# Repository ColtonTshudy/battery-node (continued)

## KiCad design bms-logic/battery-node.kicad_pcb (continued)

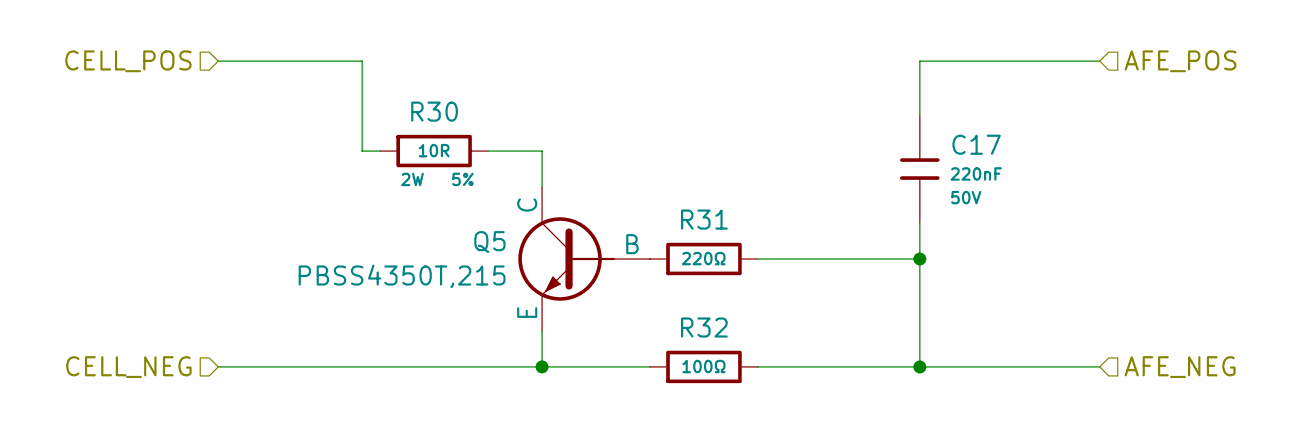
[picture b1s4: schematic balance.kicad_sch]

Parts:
C17: 220nF; C_0805; Voltage Rated 50V; Tolerance ±10%; Part CL21B224KBFNNNE; LCSC C5378
Q5: PBSS4350T,215; SOT-23; Part PBSS4350T,215
R30: 10R; R_2512_6332Metric; Tolerance 5%; Part FRP2512J100 TS
R31: 220Ω; R_0402; Tolerance ±1%; Overload Voltage (Max) 50V; Part 0402WGF2200TCE; LCSC C25091
R32: 100Ω; R_0402; Overload Voltage (Max) 50V; Tolerance ±1%; Part 0402WGF1000TCE; LCSC C25076

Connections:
/AFE/Cell1: Q5.2 (E), R32.1; also elsewhere on the board
/AFE/Cell2: R30.2; also elsewhere on the board
/AFE/VC1: C17.2, R31.2, R32.2; also elsewhere on the board
/AFE/VC2: C17.1; also elsewhere on the board
unnamed: Q5.1 (B), R31.1
unnamed: Q5.3 (C), R30.1

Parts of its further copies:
C36, C37, C38, C39, C40, C41, C42, C43, C44, C45, C46, C47, C48, C49: 220nF; C_0805; Voltage Rated 50V; Tolerance ±10%; Part CL21B224KBFNNNE; LCSC C5378
Q6, Q7, Q8, Q9, Q10, Q11, Q12, Q13, Q14, Q15, Q16, Q17, Q18, Q19: PBSS4350T,215; SOT-23; Part PBSS4350T,215
R48, R51, R54, R57, R60, R63, R66, R69, R72, R75, R78, R81, R84, R87: 10R; R_2512_6332Metric; Tolerance 5%; Part FRP2512J100 TS
R49, R52, R55, R58, R61, R64, R67, R70, R73, R76, R79, R82, R85, R88: 220Ω; R_0402; Tolerance ±1%; Overload Voltage (Max) 50V; Part 0402WGF2200TCE; LCSC C25091
R50, R53, R56, R59, R62, R65, R68, R71, R74, R77, R80, R83, R86, R89: 100Ω; R_0402; Overload Voltage (Max) 50V; Tolerance ±1%; Part 0402WGF1000TCE; LCSC C25076

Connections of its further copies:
/AFE/Cell2: Q6.2 (E), R50.1; also elsewhere on the board
/AFE/Cell3: Q7.2 (E), R48.2, R53.1; also elsewhere on the board
/AFE/Cell4: Q8.2 (E), R51.2, R56.1; also elsewhere on the board
/AFE/Cell5: Q9.2 (E), R54.2, R59.1; also elsewhere on the board
/AFE/Cell6: Q10.2 (E), R57.2, R62.1; also elsewhere on the board
/AFE/Cell7: Q11.2 (E), R60.2, R65.1; also elsewhere on the board
/AFE/Cell8: Q12.2 (E), R63.2, R68.1; also elsewhere on the board
/AFE/Cell9: Q13.2 (E), R66.2, R71.1; also elsewhere on the board
/AFE/Cell10: Q14.2 (E), R69.2, R74.1; also elsewhere on the board
/AFE/Cell11: Q15.2 (E), R72.2, R77.1; also elsewhere on the board
/AFE/Cell12: Q16.2 (E), R75.2, R80.1; also elsewhere on the board
/AFE/Cell13: Q17.2 (E), R78.2, R83.1; also elsewhere on the board
/AFE/Cell14: Q18.2 (E), R81.2, R86.1; also elsewhere on the board
/AFE/Cell15: Q19.2 (E), R84.2, R89.1; also elsewhere on the board
/AFE/Cell16: R87.2; also elsewhere on the board
/AFE/VC2: C36.2, R49.2, R50.2; also elsewhere on the board
/AFE/VC3: C36.1, C37.2, R52.2, R53.2; also elsewhere on the board
/AFE/VC4: C37.1, C38.2, R55.2, R56.2; also elsewhere on the board
/AFE/VC5: C38.1, C39.2, R58.2, R59.2; also elsewhere on the board
/AFE/VC6: C39.1, C40.2, R61.2, R62.2; also elsewhere on the board
/AFE/VC7: C40.1, C41.2, R64.2, R65.2; also elsewhere on the board
/AFE/VC8: C41.1, C42.2, R67.2, R68.2; also elsewhere on the board
/AFE/VC9: C42.1, C43.2, R70.2, R71.2; also elsewhere on the board
/AFE/VC10: C43.1, C44.2, R73.2, R74.2; also elsewhere on the board
/AFE/VC11: C44.1, C45.2, R76.2, R77.2; also elsewhere on the board
/AFE/VC12: C45.1, C46.2, R79.2, R80.2; also elsewhere on the board
/AFE/VC13: C46.1, C47.2, R82.2, R83.2; also elsewhere on the board
/AFE/VC14: C47.1, C48.2, R85.2, R86.2; also elsewhere on the board
/AFE/VC15: C48.1, C49.2, R88.2, R89.2; also elsewhere on the board
/AFE/VC16: C49.1; also elsewhere on the board
unnamed: Q6.1 (B), R49.1
unnamed: Q6.3 (C), R48.1
unnamed: Q7.1 (B), R52.1
unnamed: Q7.3 (C), R51.1
unnamed: Q8.1 (B), R55.1
unnamed: Q8.3 (C), R54.1
unnamed: Q9.1 (B), R58.1
unnamed: Q9.3 (C), R57.1
unnamed: Q10.1 (B), R61.1
unnamed: Q10.3 (C), R60.1
unnamed: Q11.1 (B), R64.1
unnamed: Q11.3 (C), R63.1
unnamed: Q12.1 (B), R67.1
unnamed: Q12.3 (C), R66.1
unnamed: Q13.1 (B), R70.1
unnamed: Q13.3 (C), R69.1
unnamed: Q14.1 (B), R73.1
unnamed: Q14.3 (C), R72.1
unnamed: Q15.1 (B), R76.1
unnamed: Q15.3 (C), R75.1
unnamed: Q16.1 (B), R79.1
unnamed: Q16.3 (C), R78.1
unnamed: Q17.1 (B), R82.1
unnamed: Q17.3 (C), R81.1
unnamed: Q18.1 (B), R85.1
unnamed: Q18.3 (C), R84.1
unnamed: Q19.1 (B), R88.1
unnamed: Q19.3 (C), R87.1

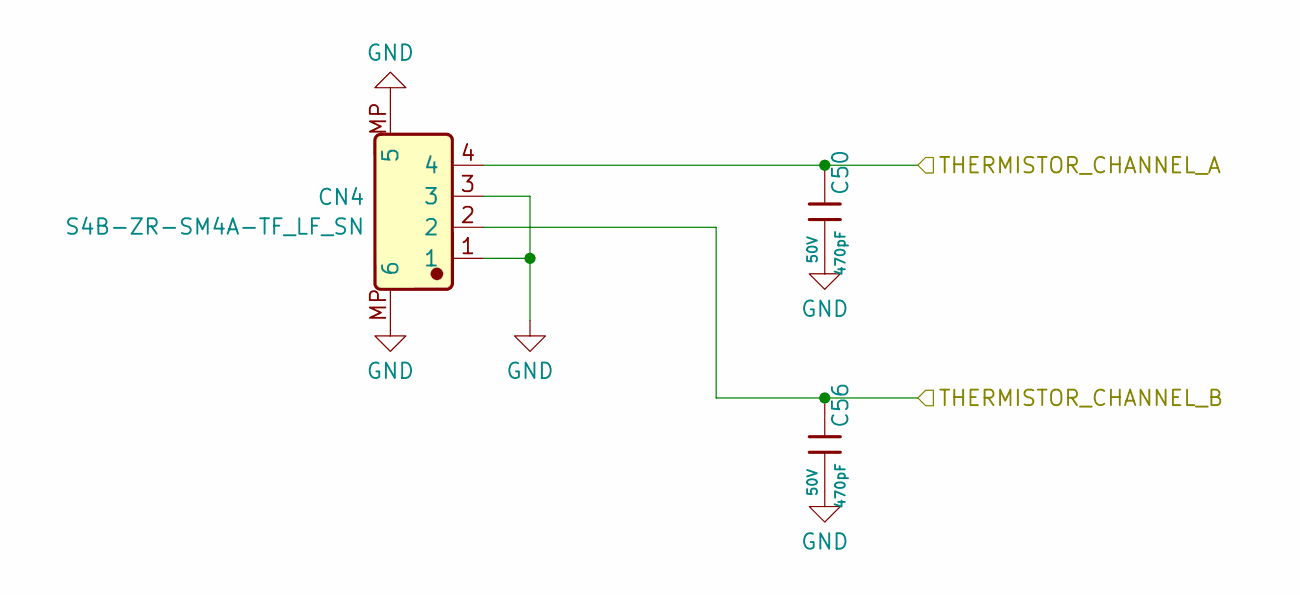
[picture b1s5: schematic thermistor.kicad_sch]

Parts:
C50, C56: 470pF; C_0402; Voltage Rated 50V; Tolerance ±10%; Part 0402B471K500NT; LCSC C1537
CN4: S4B-ZR-SM4A-TF_LF_SN; JST_ZH_S4B-ZR-SM4A-TF_1x04-1MP_P1.50mm_Horizontal; Manufacturer Part S4B-ZR-SM4A-TF(LF)(SN); LCSC C485354

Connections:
/AFE/TEMP_CELLS_1: C50.1, CN4.4; also elsewhere on the board
/AFE/TEMP_CELLS_2: C56.1, CN4.2; also elsewhere on the board
GND: C50.2, C56.2, CN4.1, CN4.3, CN4.MP (6); also elsewhere on the board

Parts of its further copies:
C51, C57: 470pF; C_0402; Voltage Rated 50V; Tolerance ±10%; Part 0402B471K500NT; LCSC C1537
CN3: S4B-ZR-SM4A-TF_LF_SN; JST_ZH_S4B-ZR-SM4A-TF_1x04-1MP_P1.50mm_Horizontal; Manufacturer Part S4B-ZR-SM4A-TF(LF)(SN); LCSC C485354

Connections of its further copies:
/AFE/TEMP_CELLS_3: C51.1, CN3.4; also elsewhere on the board
/AFE/TEMP_CELLS_4: C57.1, CN3.2; also elsewhere on the board
GND: C51.2, C57.2, CN3.1, CN3.3, CN3.MP (6); also elsewhere on the board

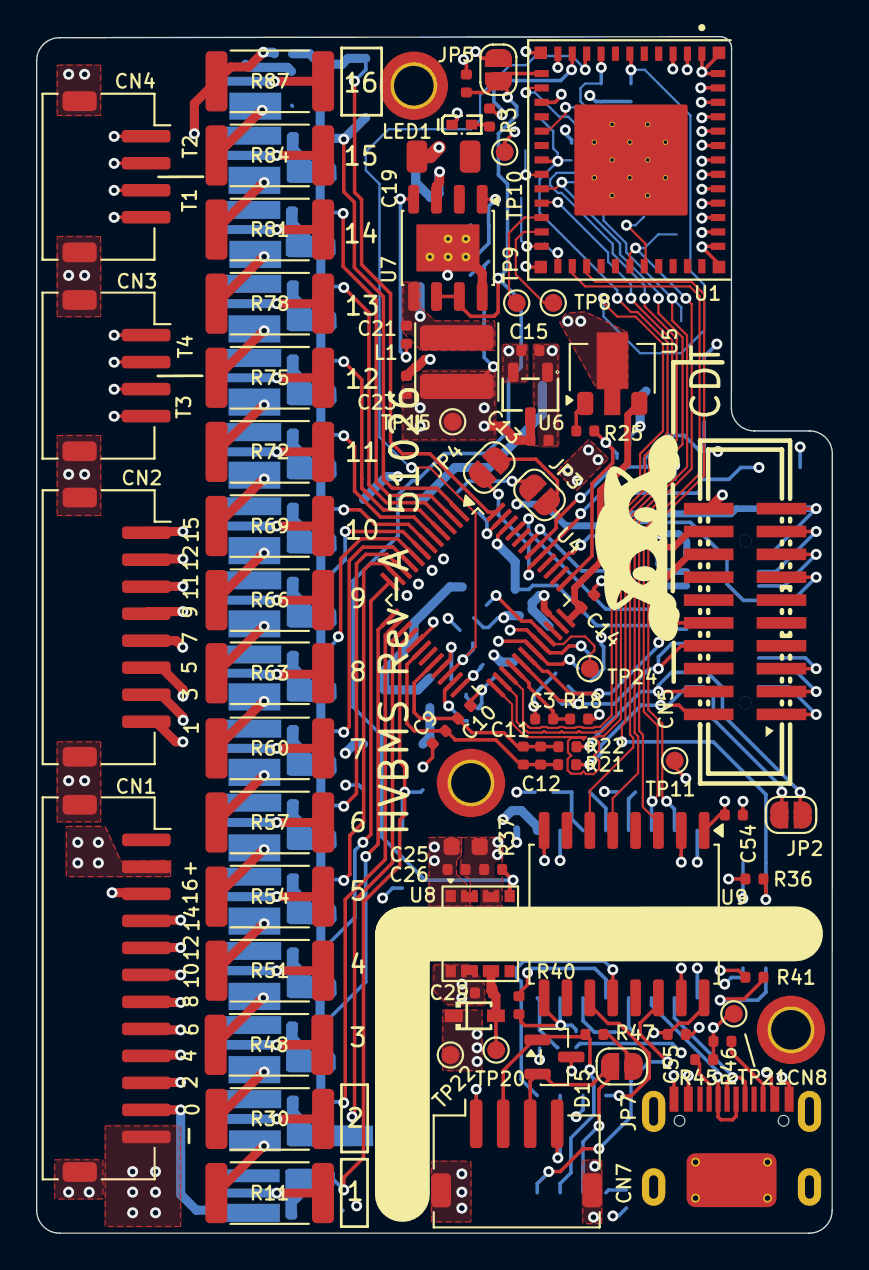
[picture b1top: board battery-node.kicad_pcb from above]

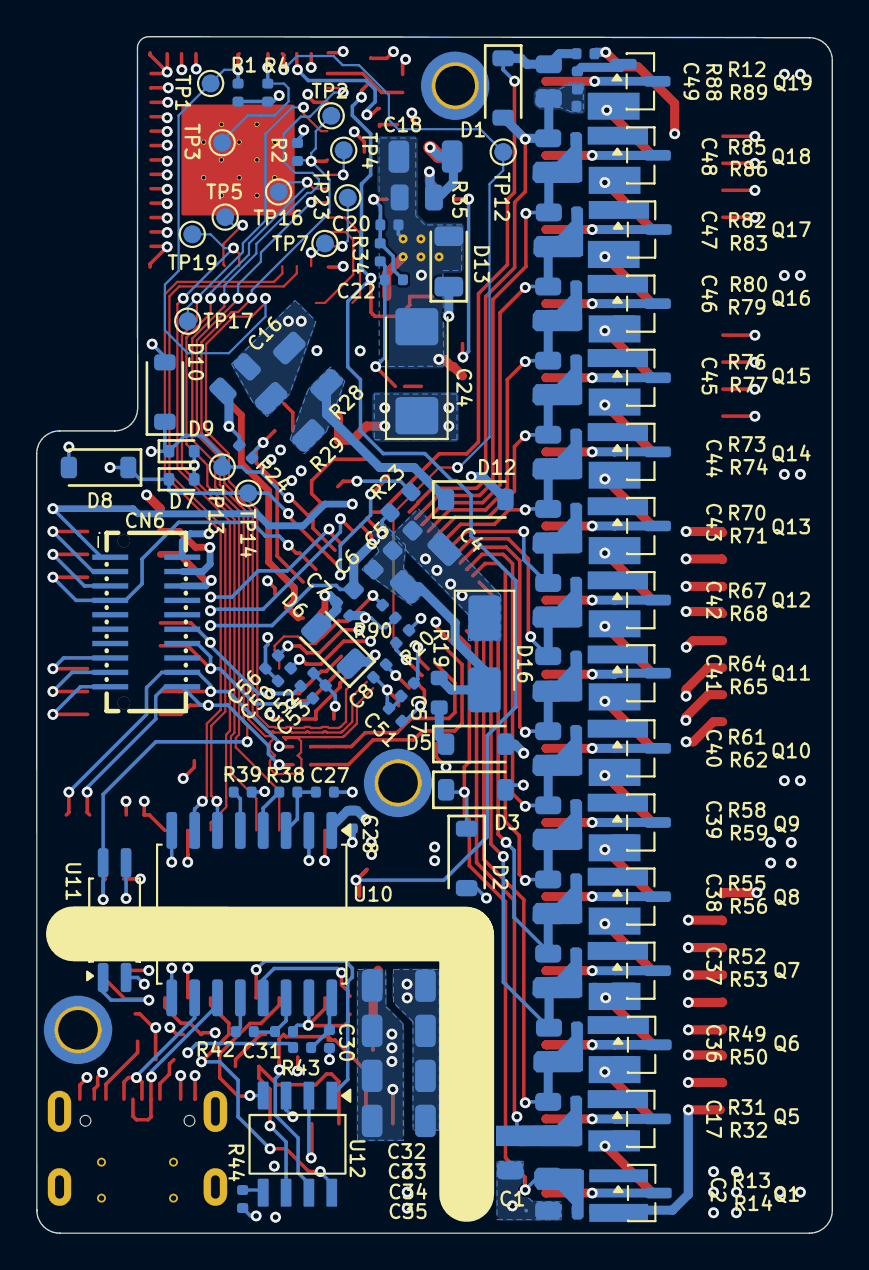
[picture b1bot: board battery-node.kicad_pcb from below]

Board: 4 copper layers, 44.2 x 66.5 mm, 216 parts (136 on the bottom side), 144 nets.

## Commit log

2025-12-06 began project
2026-01-13 Start of project
2026-01-24 Continued work on adding subcircuits for L99BM114
2026-01-25 gave untitled file a name
2026-01-25 updated to use generics for passives
2026-03-29 added BQ chip
2026-03-29 added simulations
2026-04-08 removed regulator circuit, more mosfet testing with ltspice
2026-04-09 Added new cell balancing circuit to handle 0.4 A at 4V per cell
2026-04-23 Updated simulations to fix turn-off issues at negative voltages. Added power stage to BMS based on sim 5
2026-04-27 More sims, more buildout
2026-05-02 isolated comms
2026-05-03 10.0
2026-05-03 comms updates
2026-05-03 adding diode or
2026-05-04 added precharge circuit, filled in placeholder parts
2026-05-04 force replacing main contents with 10.0 due to failed merge
2026-05-04 Revert "added precharge circuit, filled in placeholder parts"
    This reverts commit caa5444a50fe9d2ccb2e95970e40619801e9f697.
2026-05-04 rolled back TO commit caa5444, didn't mean to roll THAT back
2026-05-04 readded sims?
2026-05-04 prepping for split into 2 boards
2026-05-05 started layout
2026-05-05 readded gitignore
2026-05-05 added subdirectories
2026-05-06 started afe layout
2026-05-07 power supply layout
2026-05-08 trying to flip resistor directions (fail)
2026-05-09 diagonal
2026-05-09 cartesian
2026-05-09 old resistor array direction
2026-05-09 kicad 10.0.1 before update to .2
2026-05-10 more layout, removed some unnecessary features
2026-05-10 done with layout, need to address some DRC
